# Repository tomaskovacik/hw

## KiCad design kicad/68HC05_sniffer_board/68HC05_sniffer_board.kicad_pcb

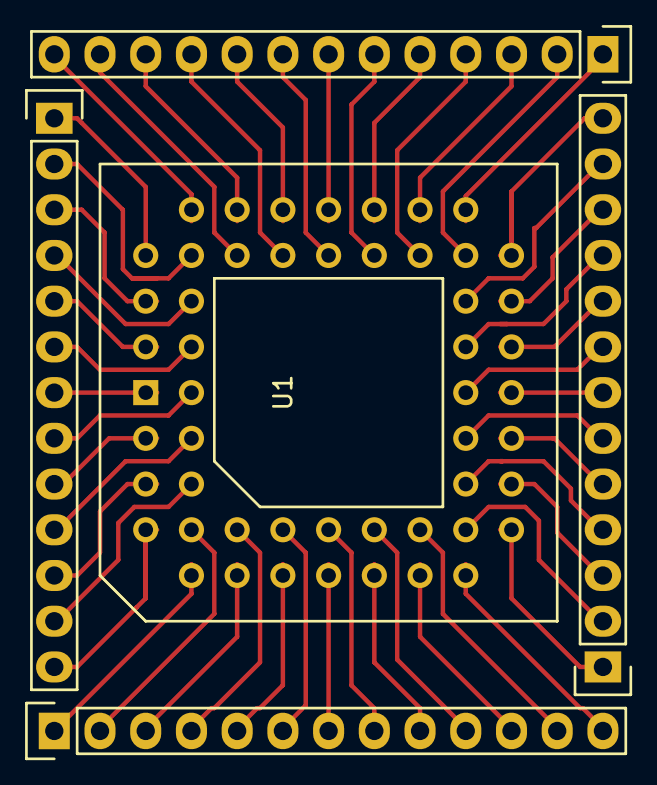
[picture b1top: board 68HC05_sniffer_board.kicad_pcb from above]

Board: 2 copper layers, 5 parts (0 on the bottom side), 52 nets.

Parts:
CON1, CON2, CON3, CON4: CONN_13; Pin_Header_Straight_1x13
U1: 68HC05_PLCC; PLCC52

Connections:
/1: CON1.7, U1.1
/2: CON1.8, U1.2
/3: CON1.9, U1.3
/4: CON1.10, U1.4
/5: CON1.11, U1.5
/6: CON1.12, U1.6
/7: CON1.13, U1.7
/8: CON2.1, U1.8
/9: CON2.2, U1.9
/10: CON2.3, U1.10
/11: CON2.4, U1.11
/12: CON2.5, U1.12
/13: CON2.6, U1.13
/14: CON2.7, U1.14
/15: CON2.8, U1.15
/16: CON2.9, U1.16
/17: CON2.10, U1.17
/18: CON2.11, U1.18
/19: CON2.12, U1.19
/20: CON2.13, U1.20
/21: CON3.1, U1.21
/22: CON3.2, U1.22
/23: CON3.3, U1.23
/24: CON3.4, U1.24
/25: CON3.5, U1.25
/26: CON3.6, U1.26
/27: CON3.7, U1.27
/28: CON3.8, U1.28
/29: CON3.9, U1.29
/30: CON3.10, U1.30
/31: CON3.11, U1.31
/32: CON3.12, U1.32
/33: CON3.13, U1.33
/34: CON4.1, U1.34
/35: CON4.2, U1.35
/36: CON4.3, U1.36
/37: CON4.4, U1.37
/38: CON4.5, U1.38
/39: CON4.6, U1.39
/40: CON4.7, U1.40
/41: CON4.8, U1.41
/42: CON4.9, U1.42
/43: CON4.10, U1.43
/44: CON4.11, U1.44
/45: CON4.12, U1.45
/46: CON4.13, U1.46
/47: CON1.1, U1.47
/48: CON1.2, U1.48
/49: CON1.3, U1.49
/50: CON1.4, U1.50
/51: CON1.5, U1.51
/52: CON1.6, U1.52

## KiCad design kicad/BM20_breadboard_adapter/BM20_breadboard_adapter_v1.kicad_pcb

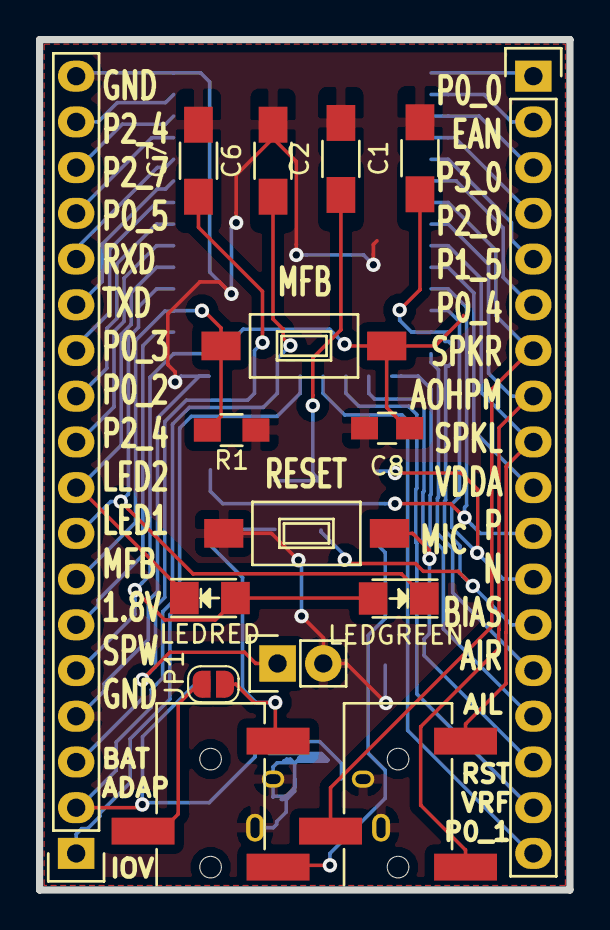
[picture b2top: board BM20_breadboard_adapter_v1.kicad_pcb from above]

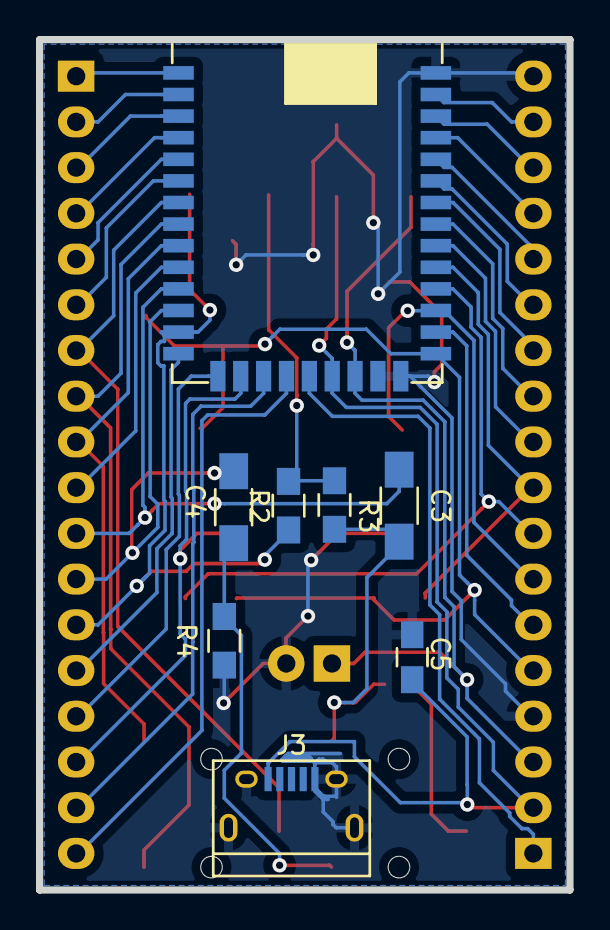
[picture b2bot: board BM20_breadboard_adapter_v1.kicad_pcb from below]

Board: 2 copper layers, 29.5 x 47.2 mm, 24 parts (8 on the bottom side), 39 nets.

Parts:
C1, C2: 2u2/10V; C_1206_HandSoldering
C3, C4: 0,1u/16V; C_1206_HandSoldering
C5, C8: 100n; C_0805_HandSoldering
C6, C7: 10u/16V; C_1206_HandSoldering
CON1, CON2: CONN_18; Pin_Header_Straight_1x18
CON3: batt; Pin_Header_Straight_1x02
D1: LEDGREEN; LED-1206
D2: LEDRED; LED-1206
J1, J2: PJ-320B; 3.5mm_stereo_jack_PJ320B
J3: USB_B_Micro; USB_Micro-B
JP1: Jumper_NO_Small; SolderJumper-2_P1.3mm_Open_RoundedPad1.0x1.5mm
R1, R2, R3: 1k; R_0805_HandSoldering
R4: 2k; R_0805_HandSoldering
SW1, SW2: SWITCH_SPST; SW_SPST_FSMSM
U1: BM20; BM20_no_silk_screen_under_antena

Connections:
/1: CON1.1, U1.1 (P0_0)
/2: CON1.2, U1.2 (EAN)
/3: CON1.3, U1.3 (P3_0)
/4: CON1.4, U1.4 (P2_0)
/5: CON1.5, U1.5 (P1_5)
/6: CON1.6, U1.6 (P0_4)
/7: CON1.7, J1.3, U1.7 (SPKR)
/8: CON1.8, J1.1, U1.8 (AOHPM)
/9: CON1.9, J1.2, U1.9 (SPKL)
/10: CON1.10, U1.10 (VDDA)
/11: C3.1, CON1.11, U1.11 (MIC1_P)
/12: C4.1, CON1.12, U1.12 (MIC1_N)
/13: C1.1, CON1.13, R2.2, U1.13 (MIC_BIAS)
/14: CON1.14, U1.14 (AIR)
/15: CON1.15, U1.15 (AIL)
/16: CON1.16, SW1.1, U1.16 (RST)
/17: CON1.17, U1.17 (VCC_RF)
/18: CON1.18, U1.18 (P0_1)
/19: CON2.1, U1.19 (VDD_IO)
/20: C5.1, C6.1, CON2.2, J3.1 (VBUS), U1.20 (ADAP_IN)
/21: C7.1, CON2.3, CON3.1, U1.21 (BAT_IN)
/24: C8.1, CON2.5, D1.2 (A), D2.2 (A), SW2.2, U1.24 (SYS_PWR)
/25: CON2.6, U1.25 (BK_OUT)
/26: CON2.7, R1.1, SW2.1, U1.26 (MFB)
/27: CON2.8, D1.1 (K), U1.27 (LED1)
/28: CON2.9, D2.1 (K), U1.28 (LED2)
/29: CON2.10, U1.29 (P2_4)
/30: CON2.11, U1.30 (P0_2)
/31: CON2.12, U1.31 (P0_3)
/32: CON2.13, U1.32 (HCI_TXD)
/33: CON2.14, U1.33 (HCI_RXD)
/34: CON2.15, U1.34 (P0_5)
/35: CON2.16, U1.35 (P2_7)
/36: CON2.17, U1.36 (P2_4)
/GND: C1.2, C2.2, C5.2, C6.2, C7.2, C8.2, CON2.4, CON2.18, CON3.2, J3.5 (GND), J3.6 (Shield), R1.2, R4.1, SW1.2, U1.22 (NC), U1.23 (GND), U1.37 (GND)
unnamed: C2.1, R2.1, R3.2
unnamed: C3.2, J2.2, JP1.2, R3.1
unnamed: C4.2, J2.1, R4.2
unnamed: J2.3, JP1.1

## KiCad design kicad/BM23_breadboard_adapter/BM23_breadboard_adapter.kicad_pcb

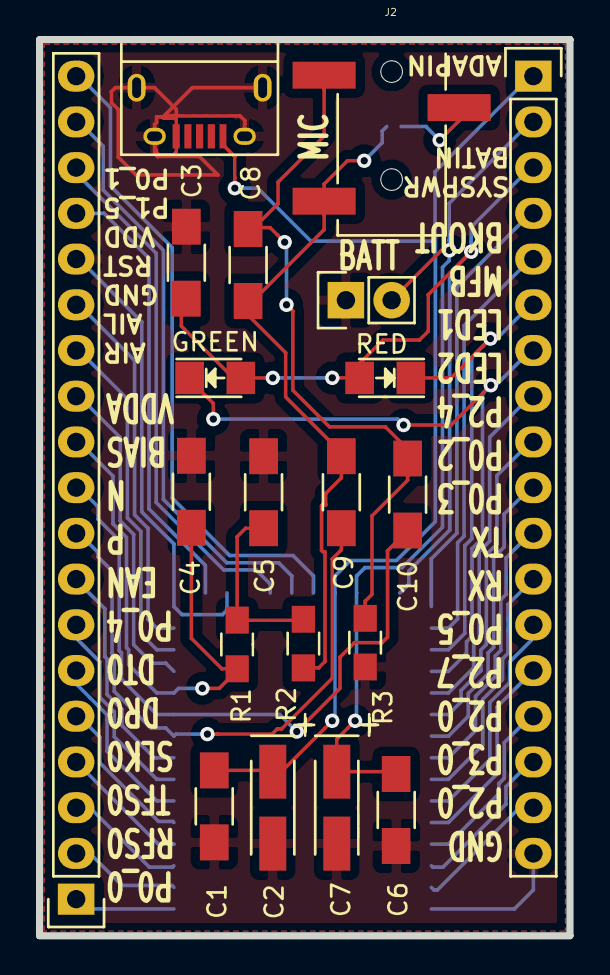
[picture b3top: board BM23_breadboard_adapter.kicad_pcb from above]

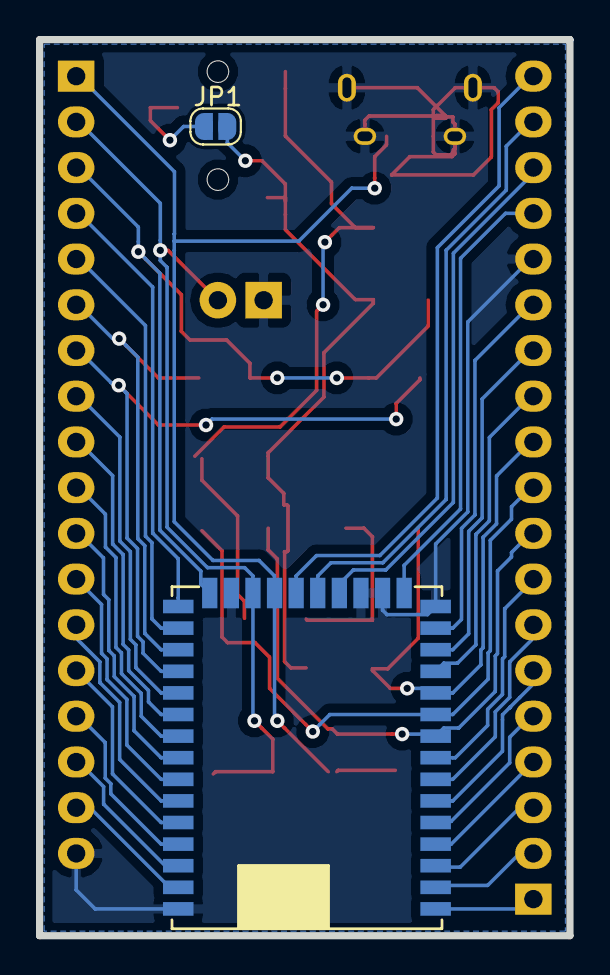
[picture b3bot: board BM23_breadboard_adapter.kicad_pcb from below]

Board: 2 copper layers, 29.5 x 49.8 mm, 22 parts (2 on the bottom side), 40 nets.

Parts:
C1, C3, C6: 100n; C_1206_HandSoldering
C2, C7: 10u/16V; TantalC_SizeA_EIA-3216_HandSoldering
C4, C5: 2.2u/6,3v; C_1206_HandSoldering
C8: 220p; C_1206_HandSoldering
C9, C10: 4.7u/16v; C_1206_HandSoldering
CON1: CONN_19; Pin_Header_Straight_1x19
CON2: CONN_18; Pin_Header_Straight_1x18
CON3: CONN_2; Pin_Header_Straight_1x02
GREEN: GREEN; LED-1206
J1: USB_B_Micro; USB_Micro-B
J2: 3.5mmjack; 3.5mm_stereo_jack_PJ320B
JP1: Jumper_NO_Small; SolderJumper-2_P1.3mm_Open_RoundedPad1.0x1.5mm
R1, R2: 1k; R_0805_HandSoldering
R3: 2k; R_0805_HandSoldering
RED: RED; LED-1206
U1: BM23; BM23_no_silk_screen_under_antena

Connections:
/1: CON1.1, U1.1
/2: CON1.2, U1.2
/3: CON1.3, U1.3
/4: CON1.4, U1.4
/5: CON1.5, U1.5
/6: CON1.6, U1.6
/7: CON1.7, U1.7
/8: CON1.8, U1.8
/9: C9.1, CON1.9, U1.9
/10: C10.1, CON1.10, U1.10
/11: C4.1, CON1.11, R1.2, U1.11
/12: CON1.12, U1.12
/13: CON1.13, U1.13
/14: CON1.14, U1.14
/15: C1.2, C2.2, C3.2, C4.2, C5.2, C6.2, C7.2, CON1.15, CON2.18, CON3.1, J1.5, J1.6, R3.1, U1.15, U1.17, U1.18, U1.24, U1.40
/16: CON1.16, U1.16
/19: CON1.17, U1.19
/20: CON1.18, U1.20
/21: CON1.19, U1.21
/22: C1.1, C2.1, CON2.1, J1.1, U1.22
/23: C6.1, C7.1, CON2.2, CON3.2, U1.23
/25: C3.1, CON2.3, GREEN.2, RED.2, U1.25
/26: CON2.4, U1.26
/27: CON2.5, U1.27
/28: CON2.6, RED.1, U1.28
/29: CON2.7, GREEN.1, U1.29
/30: CON2.8, U1.30
/31: CON2.9, U1.31
/32: CON2.10, U1.32
/33: CON2.11, U1.33
/34: CON2.12, U1.34
/35: CON2.13, U1.35
/36: CON2.14, U1.36
/37: CON2.15, U1.37
/38: CON2.16, U1.38
/39: CON2.17, U1.39
unnamed: C5.1, R1.1, R2.2
unnamed: C8.1, C9.2, J2.2, JP1.2, R2.1
unnamed: C8.2, C10.2, J2.1, R3.2
unnamed: J2.3, JP1.1
